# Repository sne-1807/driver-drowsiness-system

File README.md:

# Driver Drowsiness Detection System 

## Aim
To develop a low-cost embedded system that detects driver drowsiness using eye-blink monitoring and provides immediate alerts to driver, while enabling remote tracking of activity through IoT for enhanced road and industrial safety.

## Summary of Design
- Utilizes an ESP8266 microcontroller with an infrared eye-blink sensor to detect prolonged eye closures.
- Triggers a buzzer alert when drowsiness is detected to immediately warn the driver.
- Publishes events with timestamps to ThingSpeak, enabling cloud-based monitoring and CSV data logging.
- Powered by a 9V supply regulated to 5V using an LM7805 circuit, ensuring stable operation.

## Result
The system successfully detects abnormal eye closures and activates audible alerts, and logs each drowsiness event to ThingSpeak with real-time timestamps, exportable as CSV for analysis. Thus this project provides a scalable foundation for integration into industrial fleets or commercial vehicles.

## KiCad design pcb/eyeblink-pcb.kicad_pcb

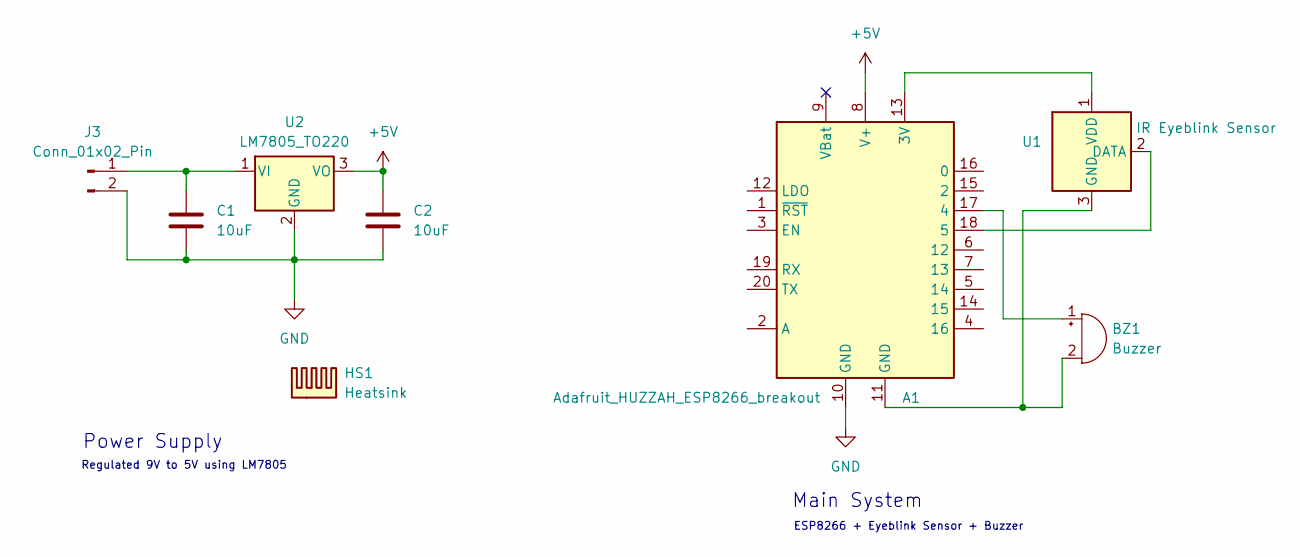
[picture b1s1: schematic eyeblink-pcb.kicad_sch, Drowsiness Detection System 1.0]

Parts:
A1: Adafruit_HUZZAH_ESP8266_breakout
BZ1: Buzzer; Buzzer_12x9.5RM7.6
C1, C2: 10uF; CP_Radial_D4.0mm_P2.00mm
HS1: Heatsink; Heatsink_Stonecold_HS-S03_13.21x12.7mm
J3: Conn_01x02_Pin; PinHeader_1x02_P1.00mm_Vertical
U1: IR Eyeblink Sensor; PinHeader_1x03_P2.54mm_Vertical
U2: LM7805_TO220; TO-220-3_Vertical

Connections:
+5V: A1.8 (V+), C2.1, U2.3 (VO)
GND: A1.10 (GND), C1.2, C2.2, J3.2, U2.2 (GND)
unnamed: A1.13 (3V), U1.1 (VDD)
unnamed: A1.17 (4), BZ1.1 (+)
unnamed: A1.18 (5), U1.2 (DATA)
unnamed: A1.11 (GND), BZ1.2 (-), U1.3 (GND)
unnamed: C1.1, J3.1, U2.1 (VI)

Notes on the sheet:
Power Supply
Regulated 9V to 5V using LM7805
ESP8266 + Eyeblink Sensor + Buzzer
Main System

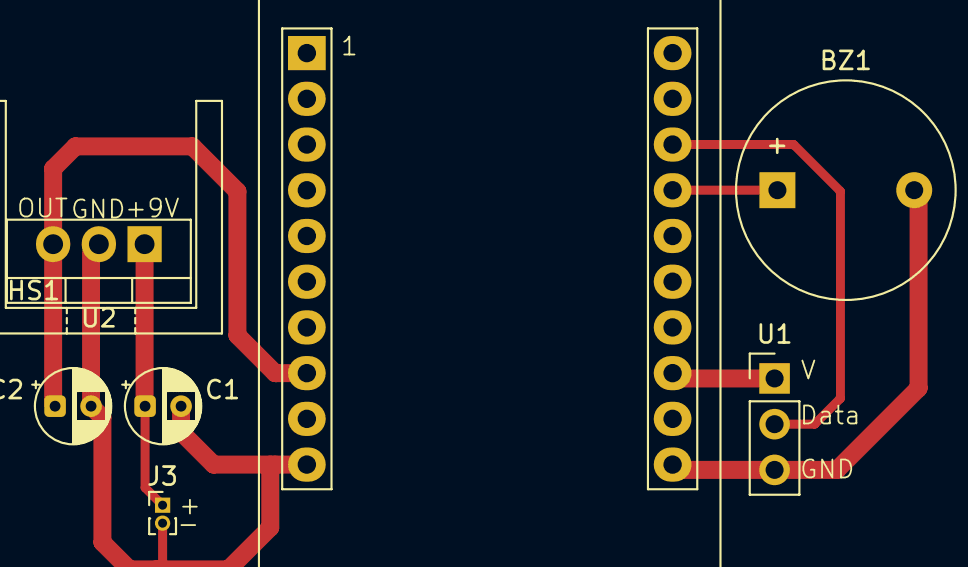
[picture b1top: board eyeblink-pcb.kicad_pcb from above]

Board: 2 copper layers, 8 parts (0 on the bottom side), 7 nets.

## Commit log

2025-07-04 Create pcb-sch
2025-07-04 Create description
2025-07-04 Create e
2025-07-04 Update documentation
2025-07-04 Create hello
2025-07-04 Update VIT_Vellore_2026
